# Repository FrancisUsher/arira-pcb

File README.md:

# Arira Keyboard PCB
Arira (아릴아) PCB designed using KiCad. This project is forked from FateNozomi's [Arisu (アリス) PCB](https://github.com/FateNozomi/arisu-pcb) design, which in turn had a layout inspired by Lyn's EM7 and TGR Alice with some modification.

This layout is designed to be a smaller (40-50%), symmetrical version of Arisu. Hence the name "Arira (아릴아)" which is also symmetrical in both English/Latin and Korean/Hangul. The symmetrical layout is intended to improve ergonomics and make the layout more friendly to users of a familiar with split-ergo keyboards. The modifier keys have been chosen to strike a balance between asthetics, symmetry, and compatibility with common existing 40-50% keyboard layouts.

Huge shoutout to FateNozomi who made their work available under the MIT license. This project preserves their original license without modification. Feel free to modify Arira as you choose and use it for any purpose.

## Gerber Files
Download the gerber files under [releases](https://github.com/FrancisUsher/arira-pcb/releases).

## Assembly
For the components required, you may refer to the bill of materials included along with the release as reference or load up the design file in KiCad.
All the components can be soldered using a regular soldering iron, though soldering the Micro USB receptacle might be the biggest hurdle.

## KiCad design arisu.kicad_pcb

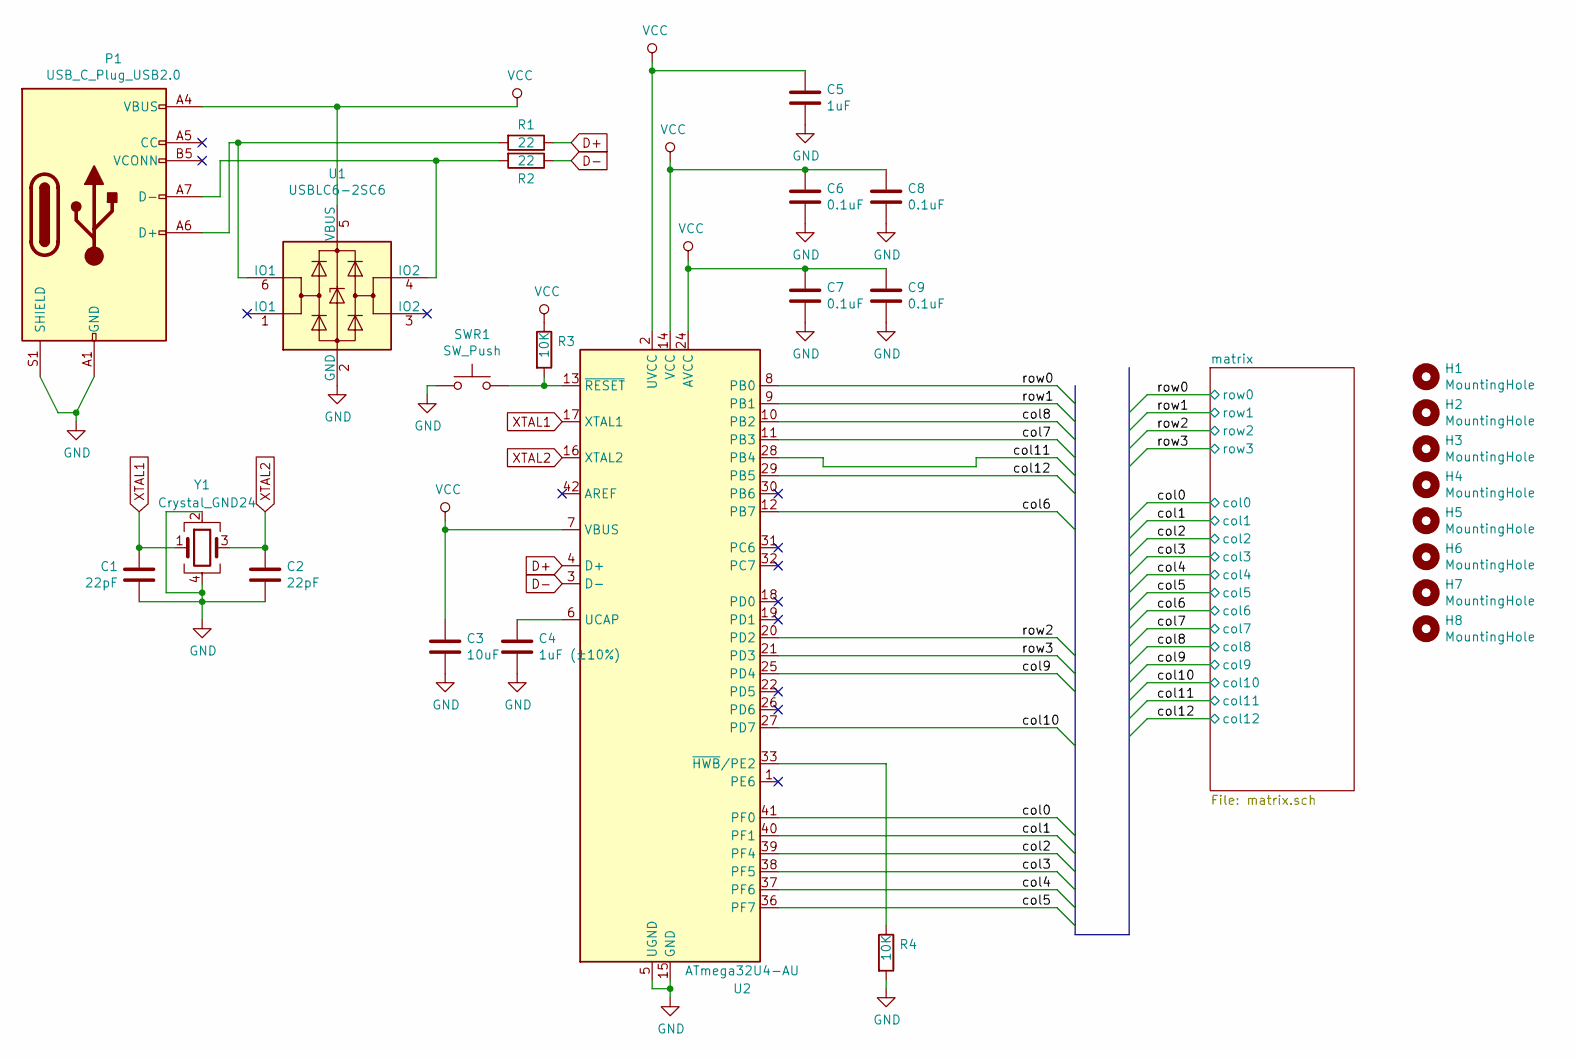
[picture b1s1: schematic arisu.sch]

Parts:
C1, C2: 22pF; C_0805_HandSoldering
C3: 10uF; C_0805_HandSoldering
C4: 1uF (±10%); C_0805_HandSoldering
C5: 1uF; C_0805_HandSoldering
C6, C7, C8, C9: 0.1uF; C_0805_HandSoldering
H1, H2, H3, H4, H5, H6, H7, H8: MountingHole; MountingHole_2.2mm_M2_Pad
P1: USB_C_Plug_USB2.0; USB_C_Receptacle_GCT_USB4085
R1, R2: 22; R_0805_HandSoldering
R3, R4: 10K; R_0805_HandSoldering
SWR1: SW_Push; SW_SPST_TL3342
U1: USBLC6-2SC6; SOT-23-6_Handsoldering
U2: ATmega32U4-AU; TQFP-44_10x10mm_Pitch0.8mm
Y1: Crystal_GND24; Crystal_SMD_SeikoEpson_FA238-4pin_3.2x2.5mm_HandSoldering

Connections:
/col0: U2.41 (PF0); also elsewhere on the board
/col1: U2.40 (PF1); also elsewhere on the board
/col2: U2.39 (PF4); also elsewhere on the board
/col3: U2.38 (PF5); also elsewhere on the board
/col4: U2.37 (PF6); also elsewhere on the board
/col5: U2.36 (PF7); also elsewhere on the board
/col6: U2.12 (PB7); also elsewhere on the board
/col7: U2.11 (PB3); also elsewhere on the board
/col8: U2.10 (PB2); also elsewhere on the board
/col9: U2.25 (PD4); also elsewhere on the board
/col10: U2.27 (PD7); also elsewhere on the board
/col11: U2.28 (PB4); also elsewhere on the board
/col12: U2.29 (PB5); also elsewhere on the board
/row0: U2.8 (PB0); also elsewhere on the board
/row1: U2.9 (PB1); also elsewhere on the board
/row2: U2.20 (PD2); also elsewhere on the board
/row3: U2.21 (PD3); also elsewhere on the board
D+: R1.1, U2.4 (D+)
D-: R2.1, U2.3 (D-)
GND: C1.1, C2.2, C3.2, C4.2, C5.2, C6.2, C7.2, C8.2, C9.2, P1.A1 (GND), P1.A12 (GND), P1.B1 (GND), P1.B12 (GND), P1.S1 (SHIELD), R4.2, SWR1.1, U1.2 (GND), U2.5 (UGND), U2.15 (GND), U2.23 (GND), U2.35 (GND), U2.43 (GND), Y1.2, Y1.4
unnamed: C4.1, U2.6 (UCAP)
unnamed: P1.A6 (D+), R1.2, U1.6 (IO1)
unnamed: P1.A7 (D-), R2.2, U1.4 (IO2)
unnamed: R3.2, SWR1.2, U2.13 (~RESET)
unnamed: R4.1, U2.33 (~HWB~/PE2)
VCC: C3.1, C5.1, C6.1, C7.1, C8.1, C9.1, P1.A4 (VBUS), P1.A9 (VBUS), P1.B4 (VBUS), P1.B9 (VBUS), R3.1, U1.5 (VBUS), U2.2 (UVCC), U2.7 (VBUS), U2.14 (VCC), U2.24 (AVCC), U2.34 (VCC), U2.44 (AVCC)
XTAL1: C1.2, U2.17 (XTAL1), Y1.1
XTAL2: C2.1, U2.16 (XTAL2), Y1.3

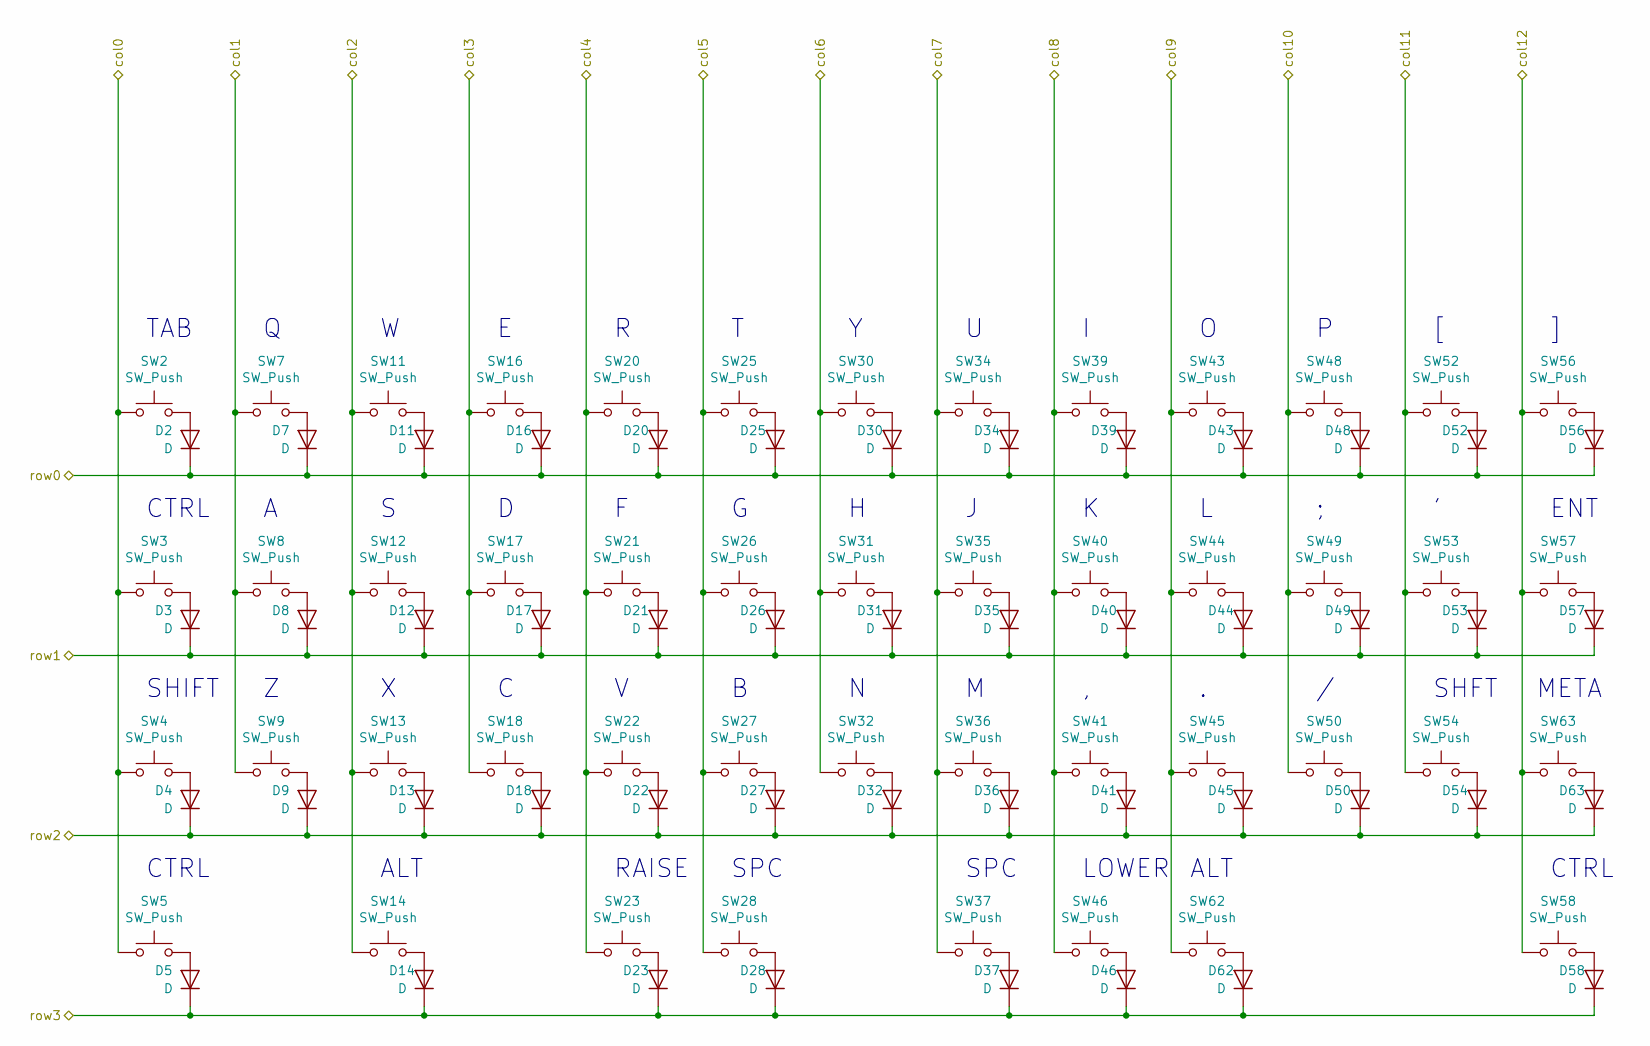
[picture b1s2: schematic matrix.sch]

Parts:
D2, D3, D4, D5, D7, D8, D9, D11, D12, D13, D14, D16, D17, D18, D20, D21, D22, D23, D25, D26, D27, D28, D30, D31, D32, D34, D35, D36, D37, D39, D40, D41, D43, D44, D45, D46, D48, D49, D50, D52, D53, D54, D56, D57, D58, D62, D63: D; D_SOD-123
SW2, SW5, SW14, SW58, SW62: SW_Push; SW_Cherry_MX_1.50u_PCB
SW3, SW54, SW57: SW_Push; SW_Cherry_MX_1.75u_PCB
SW4: SW_Push; SW_Cherry_MX_2.25u_PCB
SW7, SW8, SW9, SW11, SW12, SW13, SW16, SW17, SW18, SW20, SW21, SW22, SW23, SW25, SW26, SW27, SW30, SW31, SW32, SW34, SW35, SW36, SW39, SW40, SW41, SW43, SW44, SW45, SW46, SW48, SW49, SW50, SW52, SW53, SW56, SW63: SW_Push; SW_Cherry_MX_1.00u_PCB
SW28: SW_Push; SW_Cherry_MX_2.00u_PCB_ReversedStabilizers
SW37: SW_Push; SW_Cherry_MX_2.75u_PCB_ReversedStabilizers

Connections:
/col0: SW2.1, SW3.1, SW4.1, SW5.1; also elsewhere on the board
/col1: SW7.1, SW8.1, SW9.1; also elsewhere on the board
/col2: SW11.1, SW12.1, SW13.1, SW14.1; also elsewhere on the board
/col3: SW16.1, SW17.1, SW18.1; also elsewhere on the board
/col4: SW20.1, SW21.1, SW22.1, SW23.1; also elsewhere on the board
/col5: SW25.1, SW26.1, SW27.1, SW28.1; also elsewhere on the board
/col6: SW30.1, SW31.1, SW32.1; also elsewhere on the board
/col7: SW34.1, SW35.1, SW36.1, SW37.1; also elsewhere on the board
/col8: SW39.1, SW40.1, SW41.1, SW46.1; also elsewhere on the board
/col9: SW43.1, SW44.1, SW45.1, SW62.1; also elsewhere on the board
/col10: SW48.1, SW49.1, SW50.1; also elsewhere on the board
/col11: SW52.1, SW53.1, SW54.1; also elsewhere on the board
/col12: SW56.1, SW57.1, SW58.1, SW63.1; also elsewhere on the board
/row0: D2.1 (K), D7.1 (K), D11.1 (K), D16.1 (K), D20.1 (K), D25.1 (K), D30.1 (K), D34.1 (K), D39.1 (K), D43.1 (K), D48.1 (K), D52.1 (K), D56.1 (K); also elsewhere on the board
/row1: D3.1 (K), D8.1 (K), D12.1 (K), D17.1 (K), D21.1 (K), D26.1 (K), D31.1 (K), D35.1 (K), D40.1 (K), D44.1 (K), D49.1 (K), D53.1 (K), D57.1 (K); also elsewhere on the board
/row2: D4.1 (K), D9.1 (K), D13.1 (K), D18.1 (K), D22.1 (K), D27.1 (K), D32.1 (K), D36.1 (K), D41.1 (K), D45.1 (K), D50.1 (K), D54.1 (K), D63.1 (K); also elsewhere on the board
/row3: D5.1 (K), D14.1 (K), D23.1 (K), D28.1 (K), D37.1 (K), D46.1 (K), D58.1 (K), D62.1 (K); also elsewhere on the board
unnamed: D2.2 (A), SW2.2
unnamed: D3.2 (A), SW3.2
unnamed: D4.2 (A), SW4.2
unnamed: D5.2 (A), SW5.2
unnamed: D7.2 (A), SW7.2
unnamed: D8.2 (A), SW8.2
unnamed: D9.2 (A), SW9.2
unnamed: D11.2 (A), SW11.2
unnamed: D12.2 (A), SW12.2
unnamed: D13.2 (A), SW13.2
unnamed: D14.2 (A), SW14.2
unnamed: D16.2 (A), SW16.2
unnamed: D17.2 (A), SW17.2
unnamed: D18.2 (A), SW18.2
unnamed: D20.2 (A), SW20.2
unnamed: D21.2 (A), SW21.2
unnamed: D22.2 (A), SW22.2
unnamed: D23.2 (A), SW23.2
unnamed: D25.2 (A), SW25.2
unnamed: D26.2 (A), SW26.2
unnamed: D27.2 (A), SW27.2
unnamed: D28.2 (A), SW28.2
unnamed: D30.2 (A), SW30.2
unnamed: D31.2 (A), SW31.2
unnamed: D32.2 (A), SW32.2
unnamed: D34.2 (A), SW34.2
unnamed: D35.2 (A), SW35.2
unnamed: D36.2 (A), SW36.2
unnamed: D37.2 (A), SW37.2
unnamed: D39.2 (A), SW39.2
unnamed: D40.2 (A), SW40.2
unnamed: D41.2 (A), SW41.2
unnamed: D43.2 (A), SW43.2
unnamed: D44.2 (A), SW44.2
unnamed: D45.2 (A), SW45.2
unnamed: D46.2 (A), SW46.2
unnamed: D48.2 (A), SW48.2
unnamed: D49.2 (A), SW49.2
unnamed: D50.2 (A), SW50.2
unnamed: D52.2 (A), SW52.2
unnamed: D53.2 (A), SW53.2
unnamed: D54.2 (A), SW54.2
unnamed: D56.2 (A), SW56.2
unnamed: D57.2 (A), SW57.2
unnamed: D58.2 (A), SW58.2
unnamed: D62.2 (A), SW62.2
unnamed: D63.2 (A), SW63.2

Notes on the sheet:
TAB
CTRL
ENT
SHIFT
SHFT
ALT
RAISE
SPC
LOWER
META

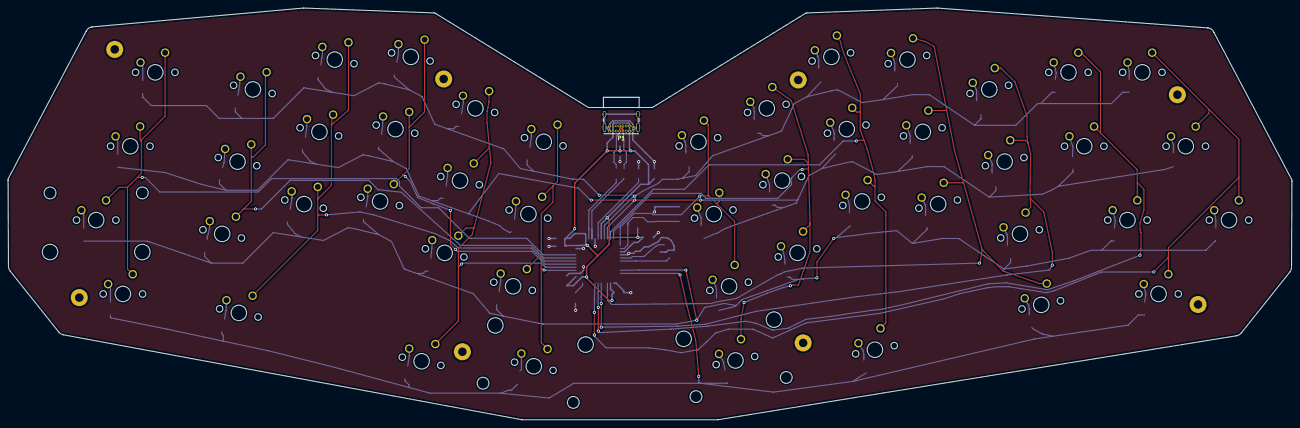
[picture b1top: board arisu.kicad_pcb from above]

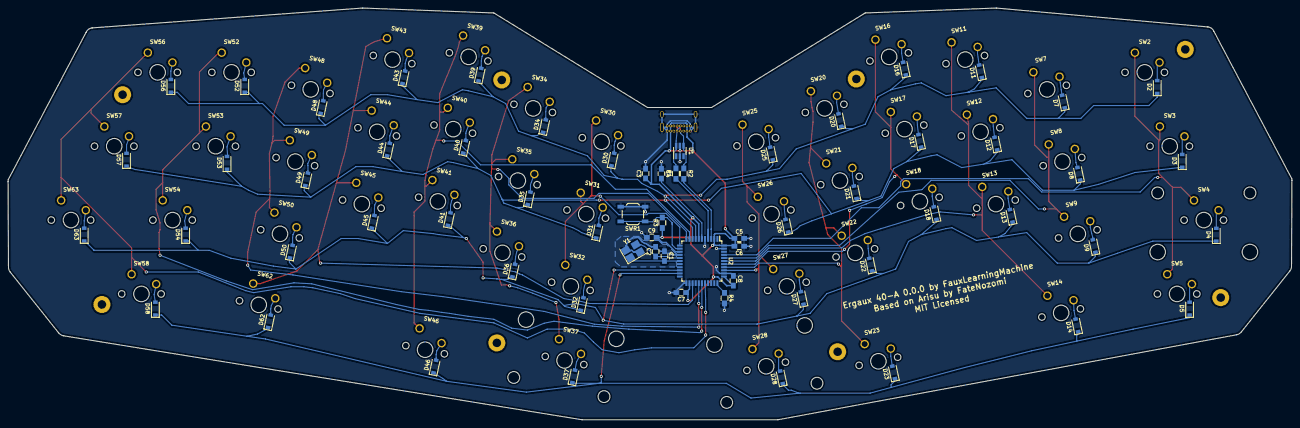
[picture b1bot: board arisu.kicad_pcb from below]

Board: 2 copper layers, 331.1 x 106.2 mm, 120 parts (64 on the bottom side), 75 nets.

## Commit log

2019-07-27 Reflect the change in project name and purpose in the docs.
2019-07-27 Remove top row and decrease all other row indexes by 1 to adjust.
2019-07-27 Begin reworking PCB layout with removed top row.
2019-07-29 Redesign alpha layout for natural finger spread.
2019-07-30 Continue making symmetrical layout.
2019-07-30 Make 69 spacebar layout lol.
2019-07-30 Make it even MORE symmetrical!
2019-07-30 Route more row tracks.
2019-07-30 Finish routing rows.
2019-07-30 Route some of the central components.
2019-07-30 Route yet more tracks.
2019-07-31 Connect a couple stray pads and complete DRC.
2019-07-31 Publish first prototype release.
2019-08-16 Start to rework for tighter layout and better ergonomicityness.
2019-08-27 Make ergo layout.
2019-08-27 Finish ergo layout and route some rows.
2019-08-27 Swap out micro-USB for USB-C 2.0
2019-08-28 Route more traces.
2019-08-28 Route a bunch of columns.
2019-08-29 Almost finish initial routing and board edge cuts.
2019-08-30 Finish edge cuts.
2019-08-30 Fix missing connection to ground on ESD module.
2019-09-06 Add a case with support for extrusion.
2019-09-06 Finalize PCB design for round 1.

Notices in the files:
arisu.kicad_pcb:
MIT Licensed
